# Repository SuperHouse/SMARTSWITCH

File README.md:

SuperHouse Home Automation SmartSwitch
=======================================

Home automation light switch that can be constructed with different
button panels, all using the same logic board. This allows the same
logic board and software to be used for either single-colour or RGB
button panels, in sizes from 1 to 4 buttons.

The switch can either operate in isolation using WiFi and local power,
or it can connect to a central light switch controller via Cat-5
cable.

It's designed to mount in a standard Australian blank wall plate,
but can also fit other types of wall plate.

Features:

 * ESP8266 with WiFi
 * RJ45 socket to allow connecting using Cat-5 cable.
 * Either single-colour or RGB buttons.
 * From 1 to 4 buttons per panel.
 * WS2811 LED controllers.

More information is available at:

  https://www.superhouse.tv/smartswitch

Hardware
--------
The "Hardware" directory contains the PCB design as an EAGLE project.
EAGLE PCB design software is available from Autodesk free for
non-commercial use.

Credits
-------
 * Jonathan Oxer <jon@oxer.com.au>

License
-------
Copyright 2014-2020 SuperHouse Automation Pty Ltd  www.superhouse.tv  

The hardware portion of this project is licensed under the TAPR Open
Hardware License (www.tapr.org/OHL). The "license" folder within this
repository contains a copy of this license in plain text format.

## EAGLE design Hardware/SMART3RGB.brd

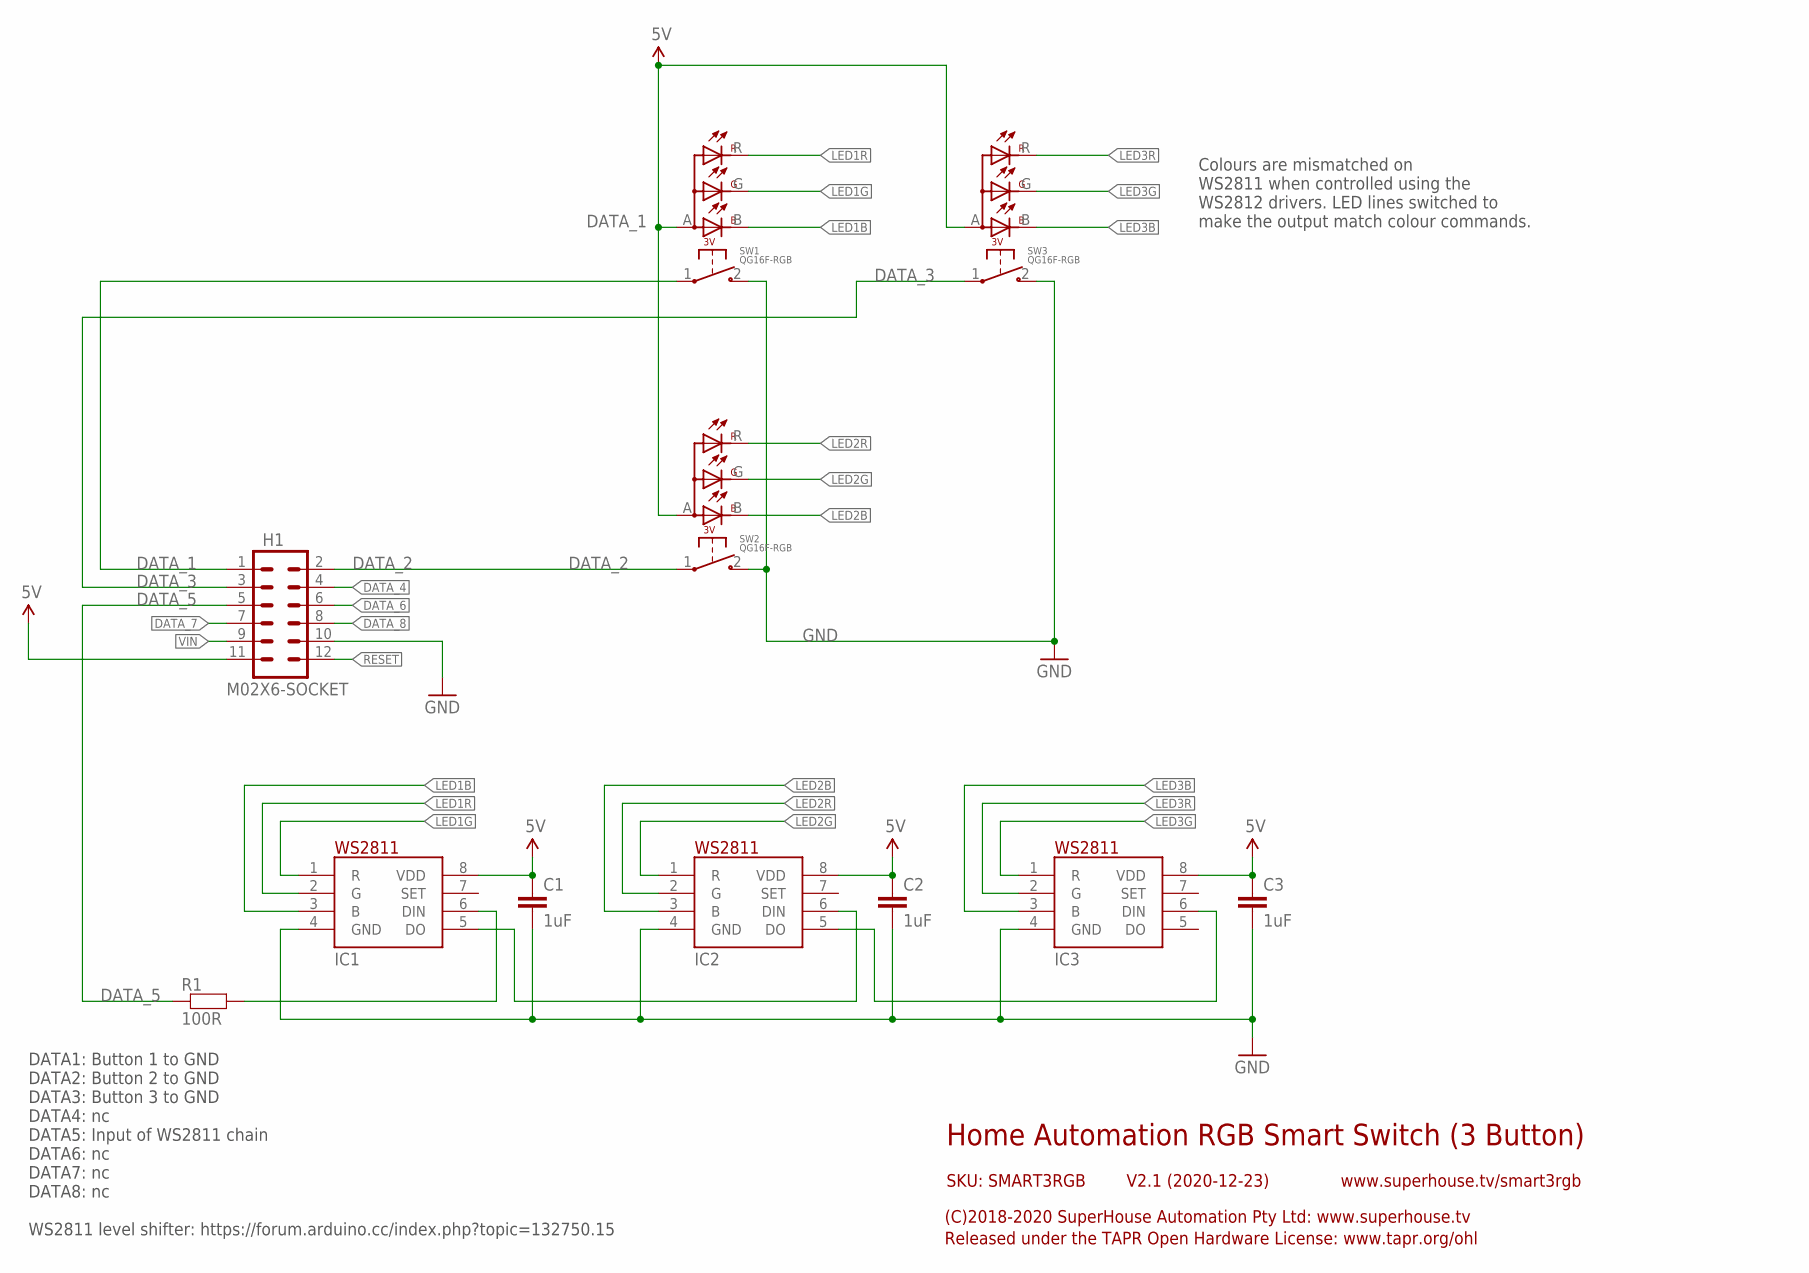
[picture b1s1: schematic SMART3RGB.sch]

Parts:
C1, C2, C3: 1uF; C0603
H1: M02X6-SOCKET; 2X06-S
IC1, IC2, IC3: WS2811-SOP8; SO08-SKINNYPADS
R1: 100R; R0603
SW1, SW2, SW3: QG16F-RGB

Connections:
5V: C1.1, C2.1, C3.1, H1.11, IC1.8 (VDD), IC2.8 (VDD), IC3.8 (VDD), SW1.A (+), SW2.A (+), SW3.A (+)
DATA_1: H1.1, SW1.1
DATA_2: H1.2, SW2.1
DATA_3: H1.3, SW3.1
DATA_4: H1.4
DATA_5: H1.5, R1.1
DATA_6: H1.6
DATA_7: H1.7
DATA_8: H1.8
GND: C1.2, C2.2, C3.2, H1.10, IC1.4 (GND), IC2.4 (GND), IC3.4 (GND), SW1.2, SW2.2, SW3.2
LED1B: IC1.3 (B), SW1.B
LED1G: IC1.1 (R), SW1.G
LED1R: IC1.2 (G), SW1.R
LED2B: IC2.3 (B), SW2.B
LED2G: IC2.1 (R), SW2.G
LED2R: IC2.2 (G), SW2.R
LED3B: IC3.3 (B), SW3.B
LED3G: IC3.1 (R), SW3.G
LED3R: IC3.2 (G), SW3.R
unnamed: IC1.6 (DIN), R1.2
unnamed: IC1.5 (DO), IC2.6 (DIN)
unnamed: IC2.5 (DO), IC3.6 (DIN)
RESET: H1.12
VIN: H1.9

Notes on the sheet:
Home Automation RGB Smart Switch (3 Button)
V2.1 (2020-12-23)
SKU: SMART3RGB
(C)2018-2020 SuperHouse Automation Pty Ltd: www.superhouse.tv
Released under the TAPR Open Hardware License: www.tapr.org/ohl
www.superhouse.tv/smart3rgb
DATA1: Button 1 to GND DATA2: Button 2 to GND DATA3: Button 3 to GND DATA4: nc DATA5: Input of WS2811 chain DATA6: nc DATA7: nc DATA8: nc WS2811 level shifter: https://forum.arduino.cc/index.php?topic=132750.15
Colours are mismatched on WS2811 when controlled using the WS2812 drivers. LED lines switched to make the output match colour commands.

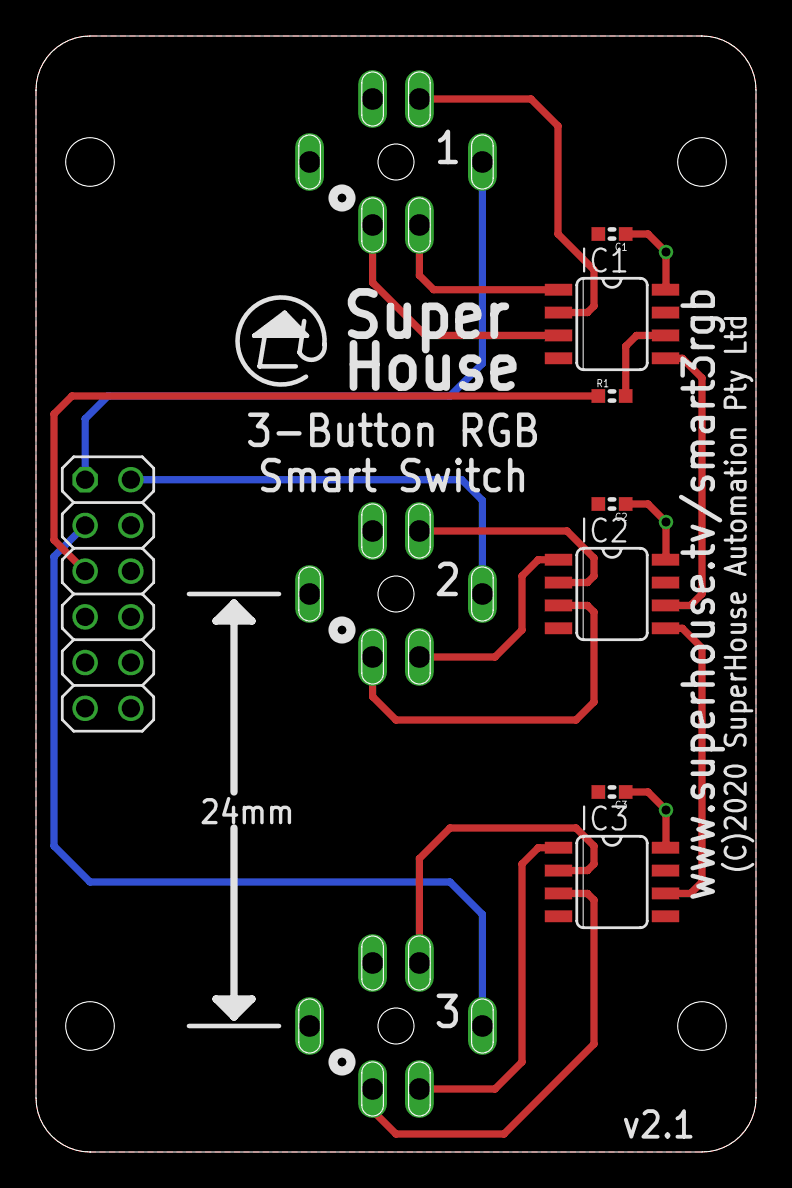
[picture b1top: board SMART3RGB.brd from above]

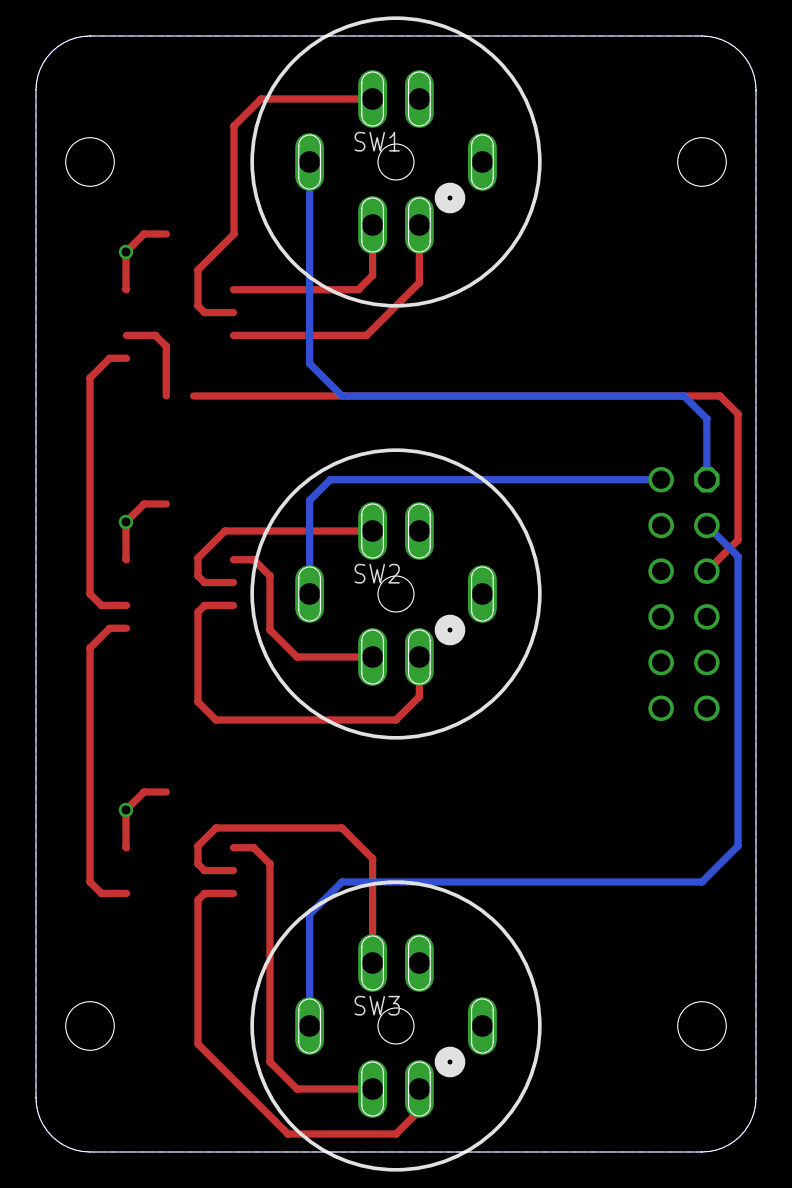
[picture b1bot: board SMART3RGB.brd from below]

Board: 2 copper layers, 40.0 x 62.0 mm, 11 parts (3 on the bottom side), 18 nets.

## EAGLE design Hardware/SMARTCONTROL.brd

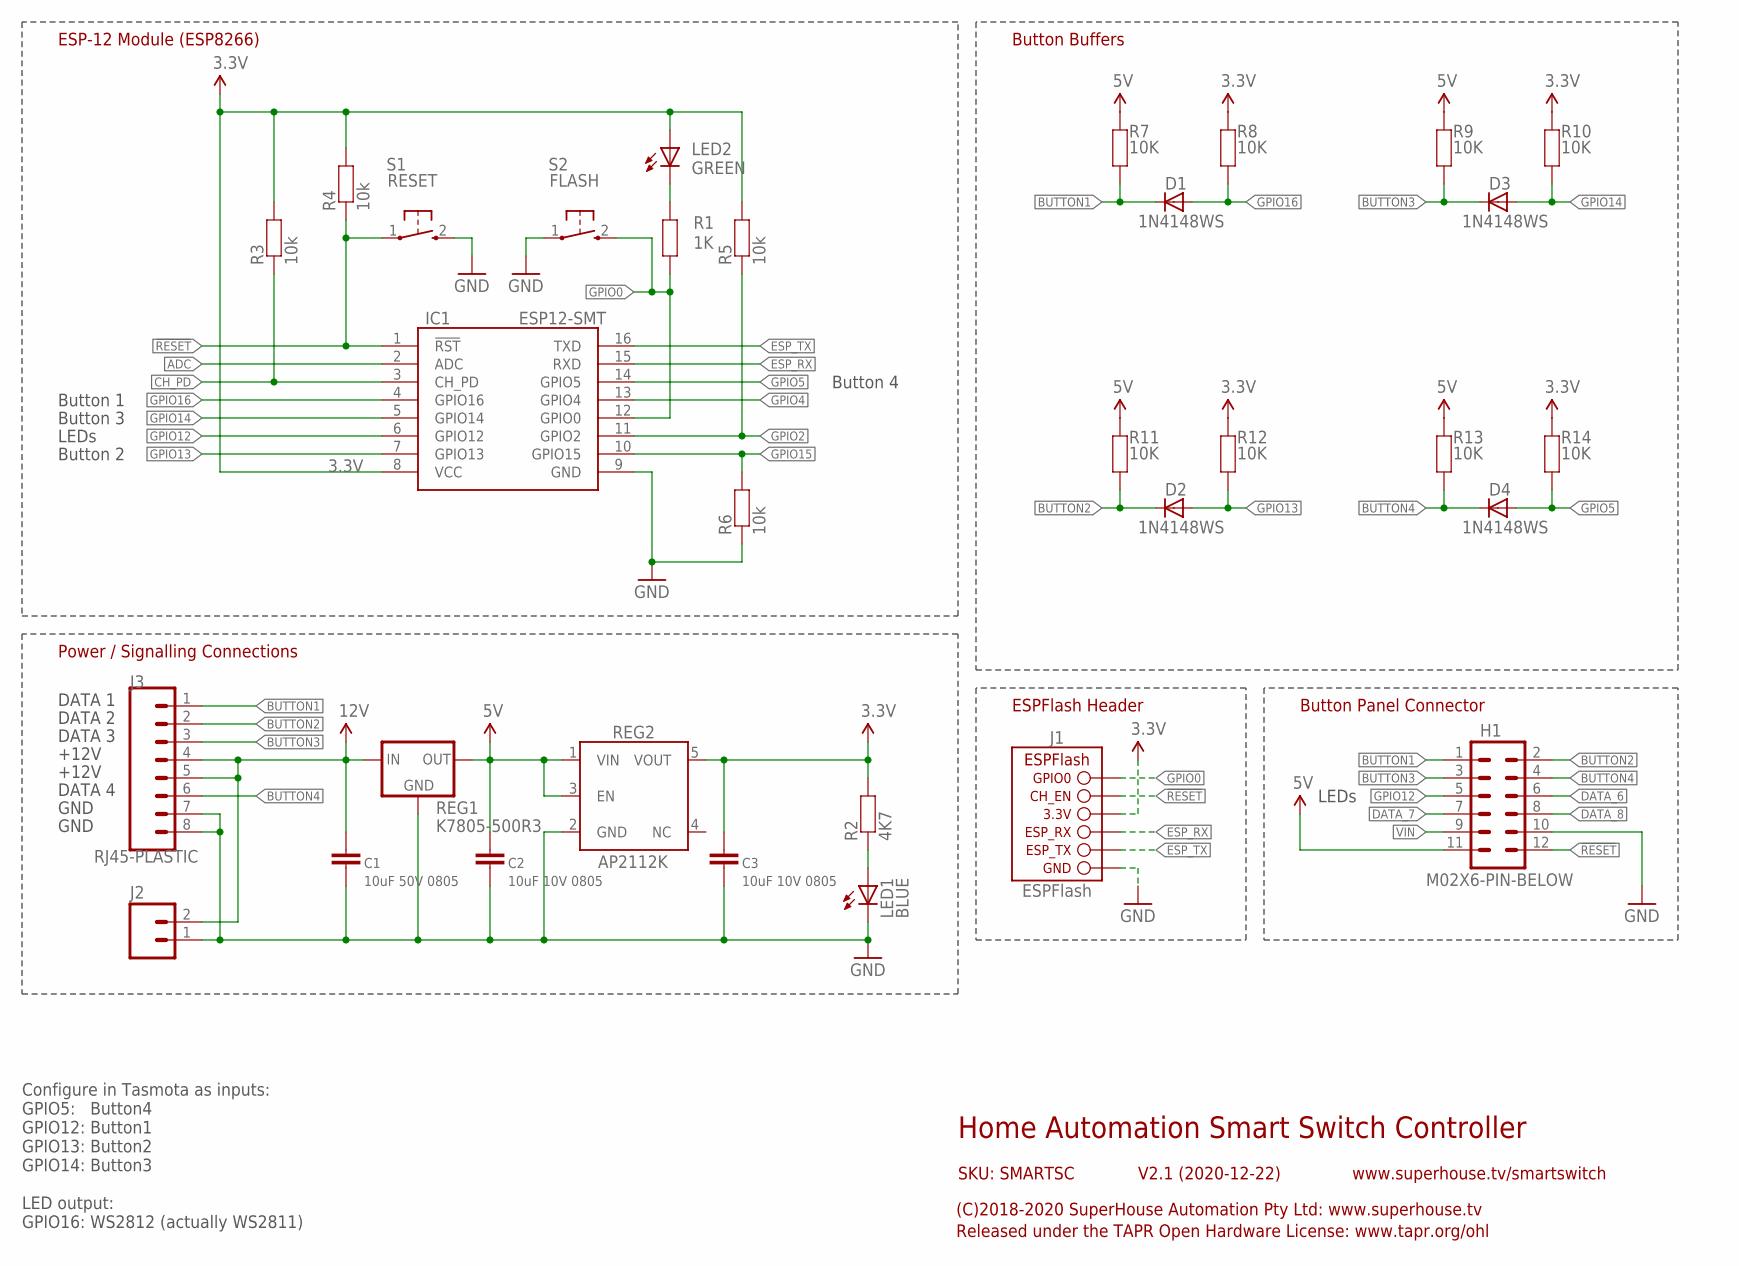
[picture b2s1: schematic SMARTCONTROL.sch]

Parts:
C1: 10uF 50V 0805; C0805
C2, C3: 10uF 10V 0805; C0805
D1, D2, D3, D4: 1N4148WS; SOD-323
H1: M02X6-PIN-BELOW; 2X06-P-BELOW
IC1: ESP12-SMT; ESP12
J1: ESPFLASH-1X6-2.54-SOCKET; 1X6-2.54-SOCKET
J2: M02-SCREW-5MM; SCREWTERMINAL-5MM-2
J3: RJ45-PLASTIC; RJ45
LED1: BLUE; LED-0603
LED2: GREEN; LED-0603
R1: 1K; R0603
R2: 4K7; R0603
R3, R4, R5, R6: 10k; R0603
R7, R8, R9, R10, R11, R12, R13, R14: 10K; R0603
REG1: K7805-500R3; K78XX-500R3
REG2: AP2112KSOT25; SOT23-5
S1: RESET; TACTILE_SMT_3X4X2
S2: FLASH; TACTILE_SMT_3X4X2

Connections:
3.3V: C3.1, IC1.8 (VCC), J1.4 (3.3V), LED2.A, R2.2, R3.2, R4.2, R5.2, R8.2, R10.2, R12.2, R14.2, REG2.5 (VOUT)
5V: C2.1, H1.11, R7.2, R9.2, R11.2, R13.2, REG1.3 (OUT), REG2.1 (VIN), REG2.3 (EN)
12V: C1.1, J2.2, J3.4, J3.5, REG1.1 (IN)
!RESET: H1.12, IC1.1 (!RST), J1.5 (CH_EN), R4.1, S1.1
ADC: IC1.2 (ADC)
BUTTON1: D1.1 (C), H1.1, J3.1, R7.1
BUTTON2: D2.1 (C), H1.2, J3.2, R11.1
BUTTON3: D3.1 (C), H1.3, J3.3, R9.1
BUTTON4: D4.1 (C), H1.4, J3.6, R13.1
CH_PD: IC1.3 (CH_PD), R3.1
DATA_6: H1.6
DATA_7: H1.7
DATA_8: H1.8
ESP_RX: IC1.15 (RXD), J1.3 (ESP_RX)
ESP_TX: IC1.16 (TXD), J1.2 (ESP_TX)
GND: C1.2, C2.2, C3.2, H1.10, IC1.9 (GND), J1.1 (GND), J2.1, J3.7, J3.8, LED1.C, R6.1, REG1.2 (GND), REG2.2 (GND), S1.2 (S), S2.1
GPIO0: IC1.12 (GPIO0), J1.6 (GPIO0), R1.2, S2.2 (S)
GPIO2: IC1.11 (GPIO2), R5.1
GPIO4: IC1.13 (GPIO4)
GPIO5: D4.2 (A), IC1.14 (GPIO5), R14.1
GPIO12: H1.5, IC1.6 (GPIO12)
GPIO13: D2.2 (A), IC1.7 (GPIO13), R12.1
GPIO14: D3.2 (A), IC1.5 (GPIO14), R10.1
GPIO15: IC1.10 (GPIO15), R6.2
GPIO16: D1.2 (A), IC1.4 (GPIO16), R8.1
unnamed: LED1.A, R2.1
unnamed: LED2.C, R1.1
VIN: H1.9

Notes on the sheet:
Home Automation Smart Switch Controller
V2.1 (2020-12-22)
SKU: SMARTSC
(C)2018-2020 SuperHouse Automation Pty Ltd: www.superhouse.tv
Released under the TAPR Open Hardware License: www.tapr.org/ohl
www.superhouse.tv/smartswitch
Configure in Tasmota as inputs: GPIO5: Button4 GPIO12: Button1 GPIO13: Button2 GPIO14: Button3 LED output: GPIO16: WS2812 (actually WS2811)
DATA 1
DATA 2
DATA 3
DATA 4
+12V
GND
Button 1
Button 2
Button 3
Button 4
LEDs
Button Panel Connector
ESP-12 Module (ESP8266)
Button Buffers
Power / Signalling Connections
ESPFlash Header

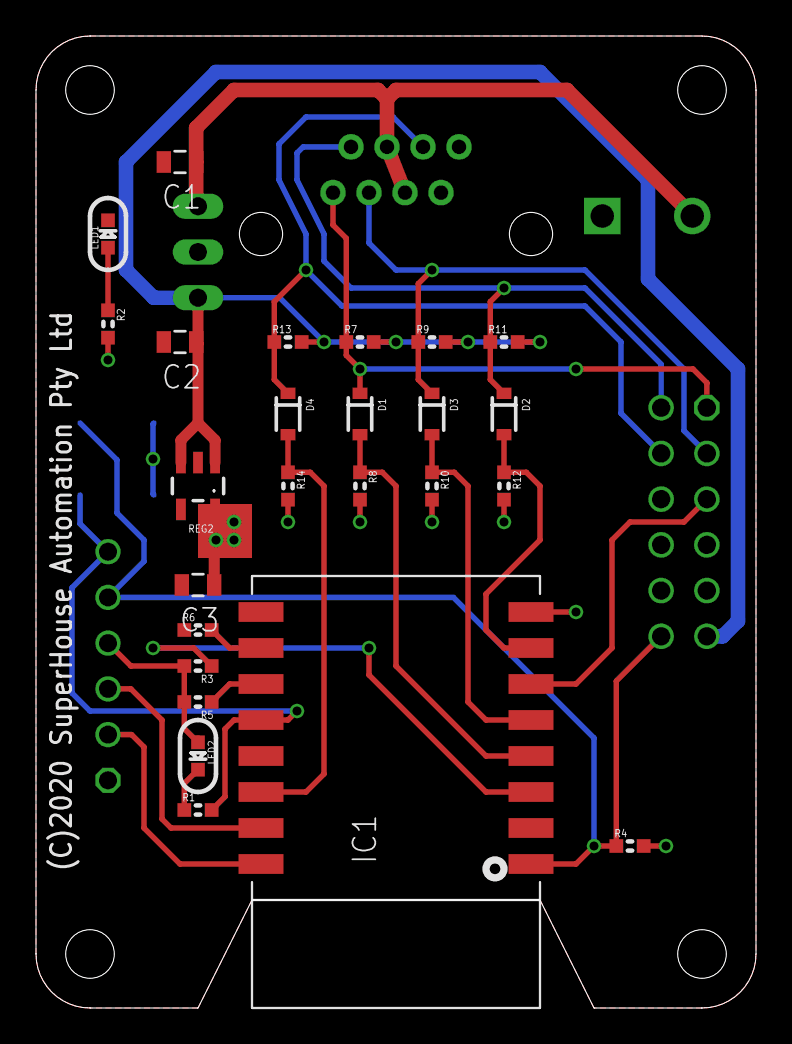
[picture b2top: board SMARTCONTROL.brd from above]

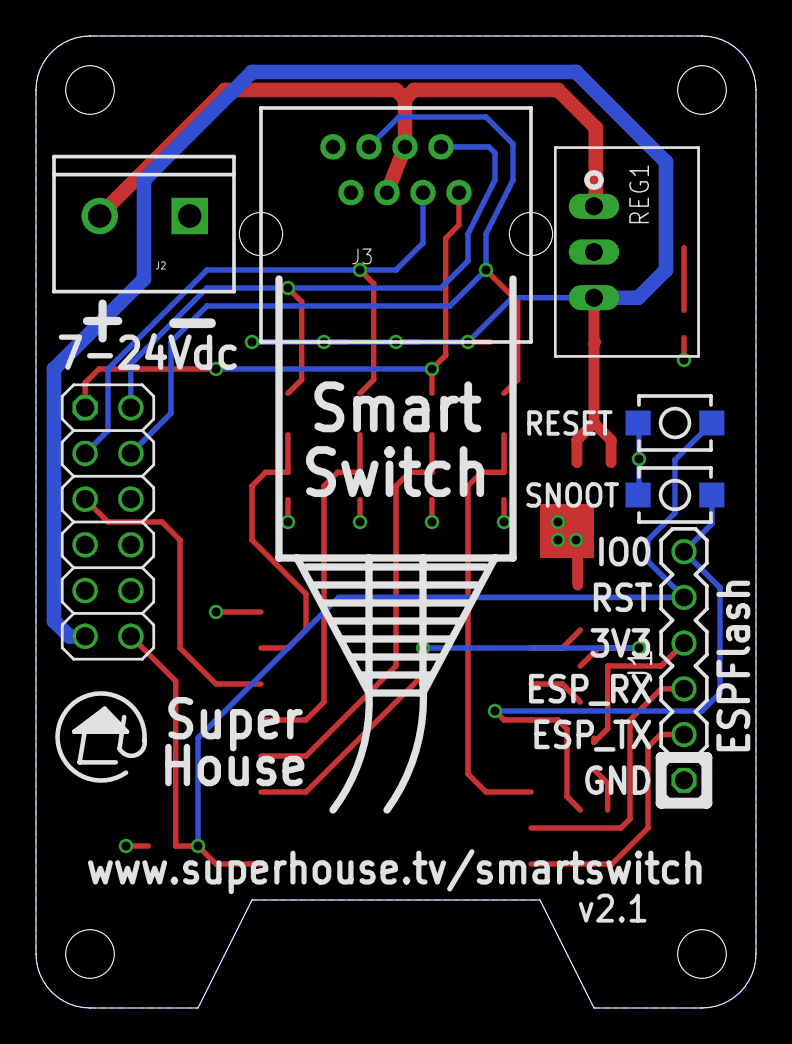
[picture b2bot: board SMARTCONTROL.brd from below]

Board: 2 copper layers, 40.0 x 54.0 mm, 32 parts (7 on the bottom side), 22 nets.

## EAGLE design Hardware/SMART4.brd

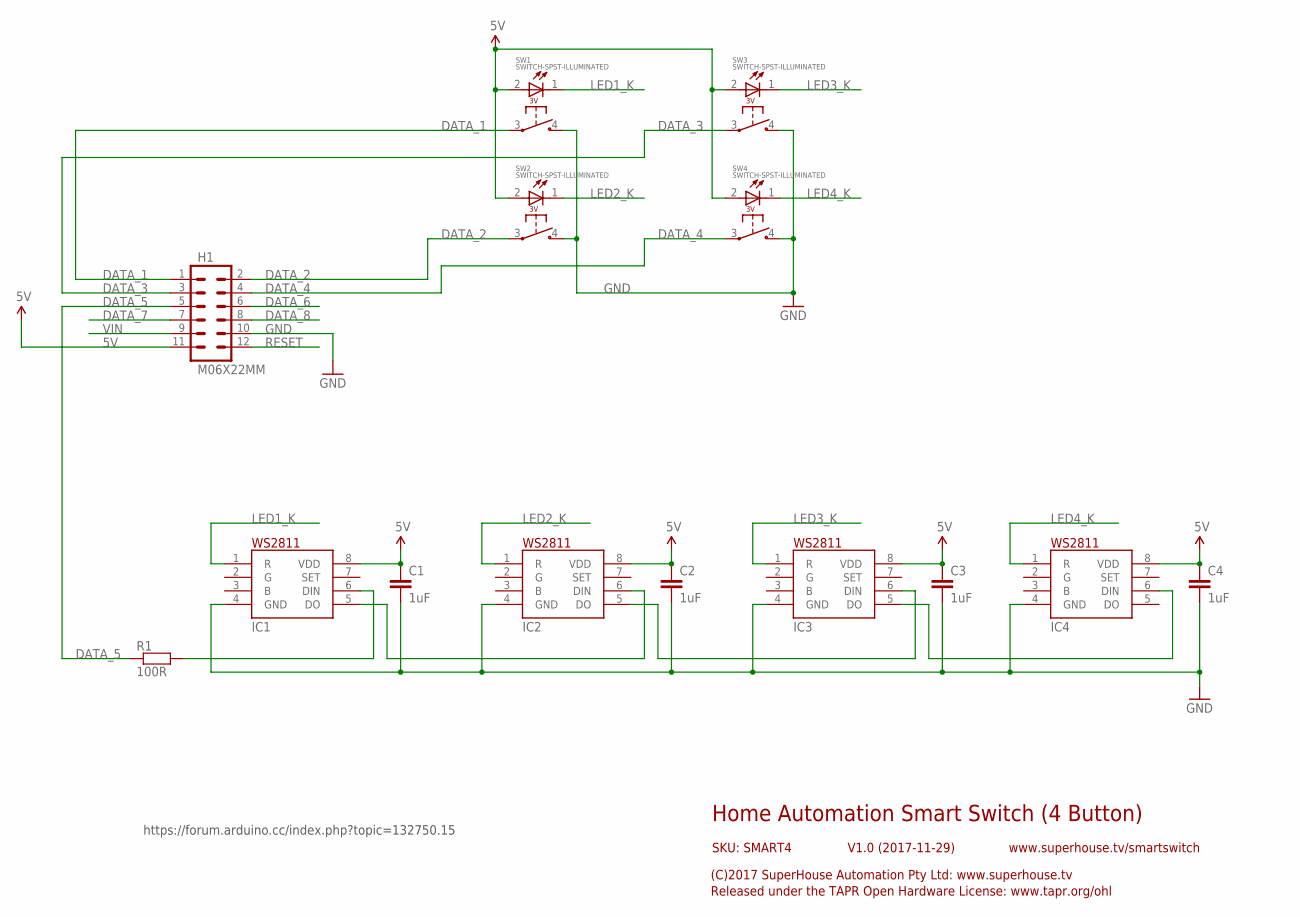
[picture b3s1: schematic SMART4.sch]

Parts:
C1, C2, C3, C4: 1uF; 0603
H1: M06X22MM; 2X6-2MM
IC1, IC2, IC3, IC4: WS2811-SOP8; SO08-SKINNYPADS
R1: 100R; 0603
SW1, SW2, SW3, SW4: SWITCH-SPST-ILLUMINATED

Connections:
5V: C1.1, C2.1, C3.1, C4.1, H1.11, IC1.8 (VDD), IC2.8 (VDD), IC3.8 (VDD), IC4.8 (VDD), SW1.2 (+), SW2.2 (+), SW3.2 (+), SW4.2 (+)
DATA_1: H1.1, SW1.3 (COM)
DATA_2: H1.2, SW2.3 (COM)
DATA_3: H1.3, SW3.3 (COM)
DATA_4: H1.4, SW4.3 (COM)
DATA_5: H1.5, R1.1
DATA_6: H1.6
DATA_7: H1.7
DATA_8: H1.8
GND: C1.2, C2.2, C3.2, C4.2, H1.10, IC1.4 (GND), IC2.4 (GND), IC3.4 (GND), IC4.4 (GND), SW1.4 (NO), SW2.4 (NO), SW3.4 (NO), SW4.4 (NO)
LED1_K: IC1.1 (R), SW1.1 (-)
LED2_K: IC2.1 (R), SW2.1 (-)
LED3_K: IC3.1 (R), SW3.1 (-)
LED4_K: IC4.1 (R), SW4.1 (-)
unnamed: IC1.6 (DIN), R1.2
unnamed: IC1.5 (DO), IC2.6 (DIN)
unnamed: IC2.5 (DO), IC3.6 (DIN)
unnamed: IC3.5 (DO), IC4.6 (DIN)
RESET: H1.12
VIN: H1.9

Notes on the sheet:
Home Automation Smart Switch (4 Button)
V1.0 (2017-11-29)
SKU: SMART4
(C)2017 SuperHouse Automation Pty Ltd: www.superhouse.tv
Released under the TAPR Open Hardware License: www.tapr.org/ohl
www.superhouse.tv/smartswitch
https://forum.arduino.cc/index.php?topic=132750.15

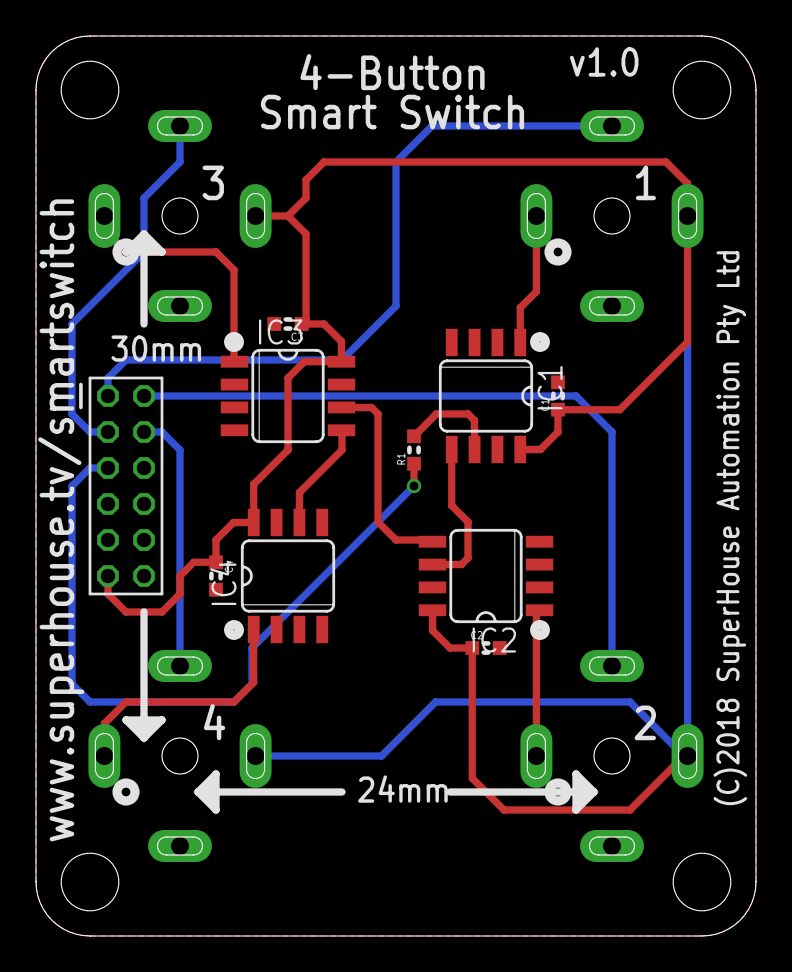
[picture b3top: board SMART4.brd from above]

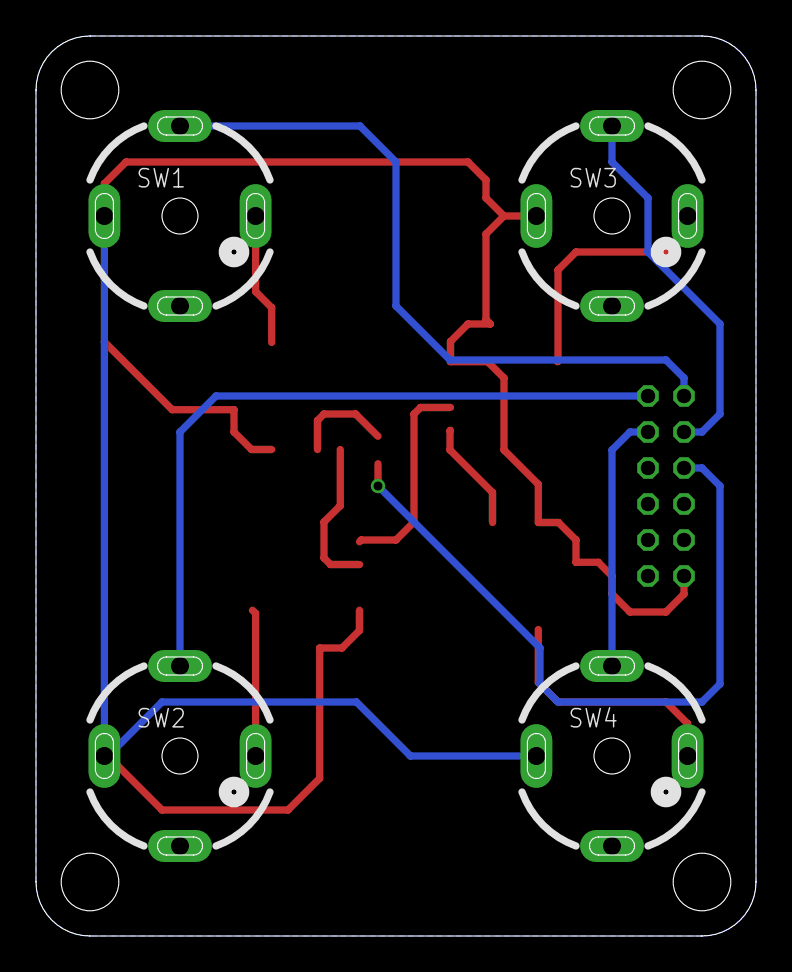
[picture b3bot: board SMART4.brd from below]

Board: 2 copper layers, 40.0 x 50.0 mm, 14 parts (4 on the bottom side), 15 nets.

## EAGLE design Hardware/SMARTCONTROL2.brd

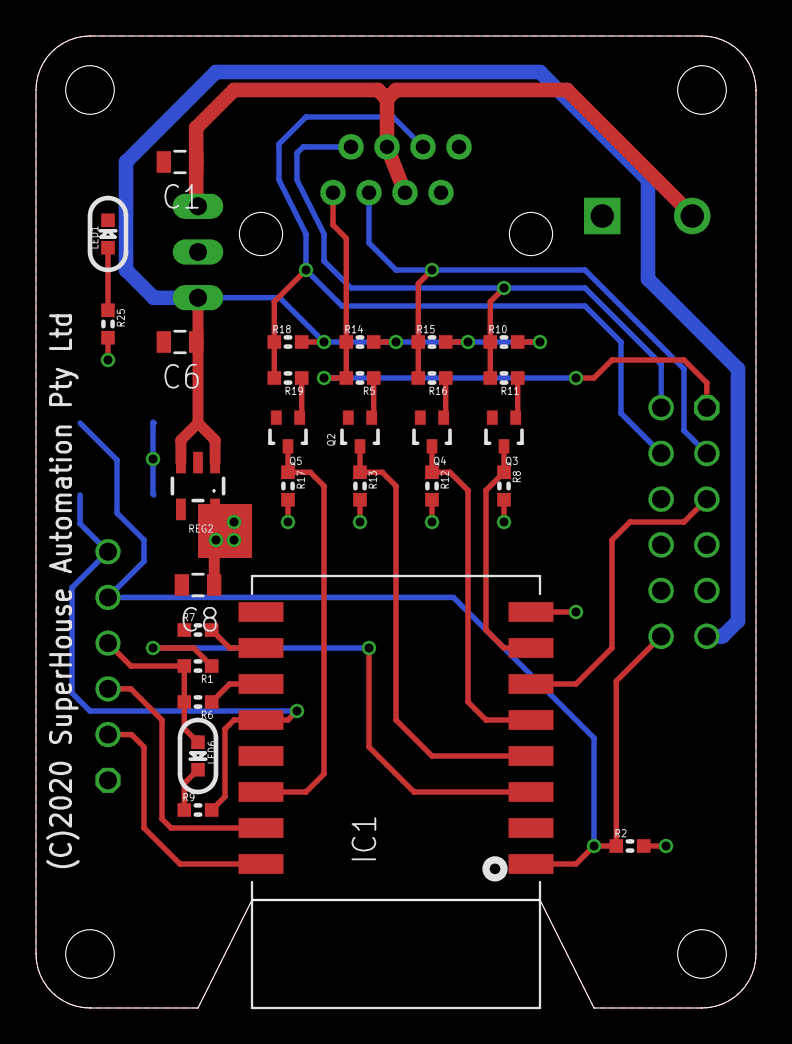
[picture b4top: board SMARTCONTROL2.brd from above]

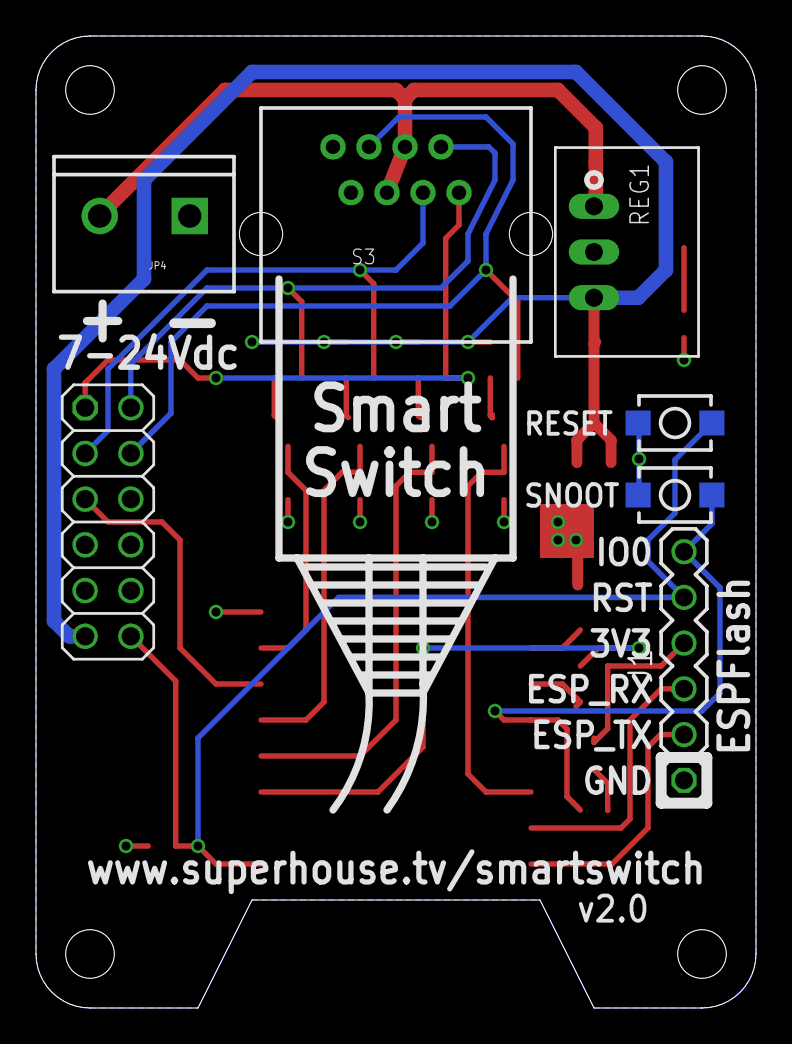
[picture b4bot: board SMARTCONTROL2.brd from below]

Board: 2 copper layers, 40.0 x 54.0 mm, 36 parts (7 on the bottom side), 26 nets.

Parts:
C1: 10uF 50V 0805; C0805
C6, C8: 10uF 10V 0805; C0805
H1: M02X6-PIN-BELOW; 2X06-P-BELOW
IC1: ESP12-SMT; ESP12
J1: ESPFLASH-1X6-2.54-SOCKET; 1X6-2.54-SOCKET
JP4: SCREWTERMINAL-5MM-2
LED1: BLUE; LED-0603
LED6: GREEN; LED-0603
Q2, Q3, Q4, Q5: RJU003N03; SOT32-3
R1, R2, R6, R7: 10k; R0603
R5, R9, R11, R16, R19: 1K; R0603
R8, R10, R12, R13, R14, R15, R17, R18: 22K; R0603
R25: 4K7; R0603
REG1: K7805-500R3; K78XX-500R3
REG2: AP2112KSOT25; SOT23-5
S1: RESET; TACTILE_SMT_3X4X2
S2: FLASH; TACTILE_SMT_3X4X2
S3: RJ45-PLASTIC; RJ45

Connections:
3.3V: C8.1, IC1.8, J1.4, LED6.A, R1.2, R2.2, R6.2, R8.2, R12.2, R13.2, R17.2, R25.2, REG2.5
5V: C6.1, H1.11, R10.2, R14.2, R15.2, R18.2, REG1.3, REG2.1, REG2.3
12V: C1.1, JP4.2, REG1.1, S3.4, S3.5
!RESET: H1.12, IC1.1, J1.5, R2.1, S1.1
BUTTON1: H1.1, R5.2, R14.1, S3.1
BUTTON2: H1.2, R10.1, R11.2, S3.2
BUTTON3: H1.3, R15.1, R16.2, S3.3
BUTTON4: H1.4, R18.1, R19.2, S3.6
CH_PD: IC1.3, R1.1
ESP_RX: IC1.15, J1.3
ESP_TX: IC1.16, J1.2
GND: C1.2, C6.2, C8.2, H1.10, IC1.9, J1.1, JP4.1, LED1.C, Q2.2, Q3.2, Q4.2, Q5.2, R7.1, REG1.2, REG2.2, S1.2, S2.1, S3.7, S3.8
GPIO0: IC1.12, J1.6, R9.2, S2.2
GPIO2: IC1.11, R6.1
GPIO5: IC1.14, Q5.3, R17.1
GPIO12: H1.5, IC1.6
GPIO13: IC1.7, Q3.3, R8.1
GPIO14: IC1.5, Q4.3, R12.1
GPIO15: IC1.10, R7.2
GPIO16: IC1.4, Q2.3, R13.1
unnamed: Q2.1, R5.1
unnamed: Q3.1, R11.1
unnamed: Q4.1, R16.1
unnamed: Q5.1, R19.1
unnamed: LED1.A, R25.1
unnamed: LED6.C, R9.1

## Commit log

2020-10-21 Merged separate projects into one common SmartSwitch project
2020-10-21 Replaced 3.3V regulator. Switched button1 and LED pins. Extended PCB to improve bolt clearance. Changed bottom layer to 3.3V.
2020-10-21 Updated timesheet.
2020-10-25 Routing for expanded PCB.
2020-10-26 Created alternative version of board with parts underneath.
2020-10-26 Routing.
2020-10-26 Added more preview images.
2020-11-06 Moved v2 board back to original name, and finished ERC/DRC for v2.0 release.
2020-11-06 Alter size of board and hole locations to match updated controller. Switch green and blue connections to make colours match WS2812 profile.
2020-11-06 Update F360 link.
2020-11-06 Added .gitignore.
2020-11-06 Removed timesheet.
2020-11-06 Forked 4-button version to make 3-button version.
2020-11-07 Routing, ERC, and DRC for v2.0 release.
2020-11-07 Duplicated project files for 2-button version.
2020-11-07 Final routing, ERC, and DRC for v2.0 release.
2021-01-04 Converted switch isolation from FETs to diodes for v2.1 release.
2021-06-08 Renamed render.

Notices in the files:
Hardware/SMART3RGB.brd:
(C)2020 SuperHouse Automation Pty Ltd
Hardware/SMART4.brd:
(C)2018 SuperHouse Automation Pty Ltd
